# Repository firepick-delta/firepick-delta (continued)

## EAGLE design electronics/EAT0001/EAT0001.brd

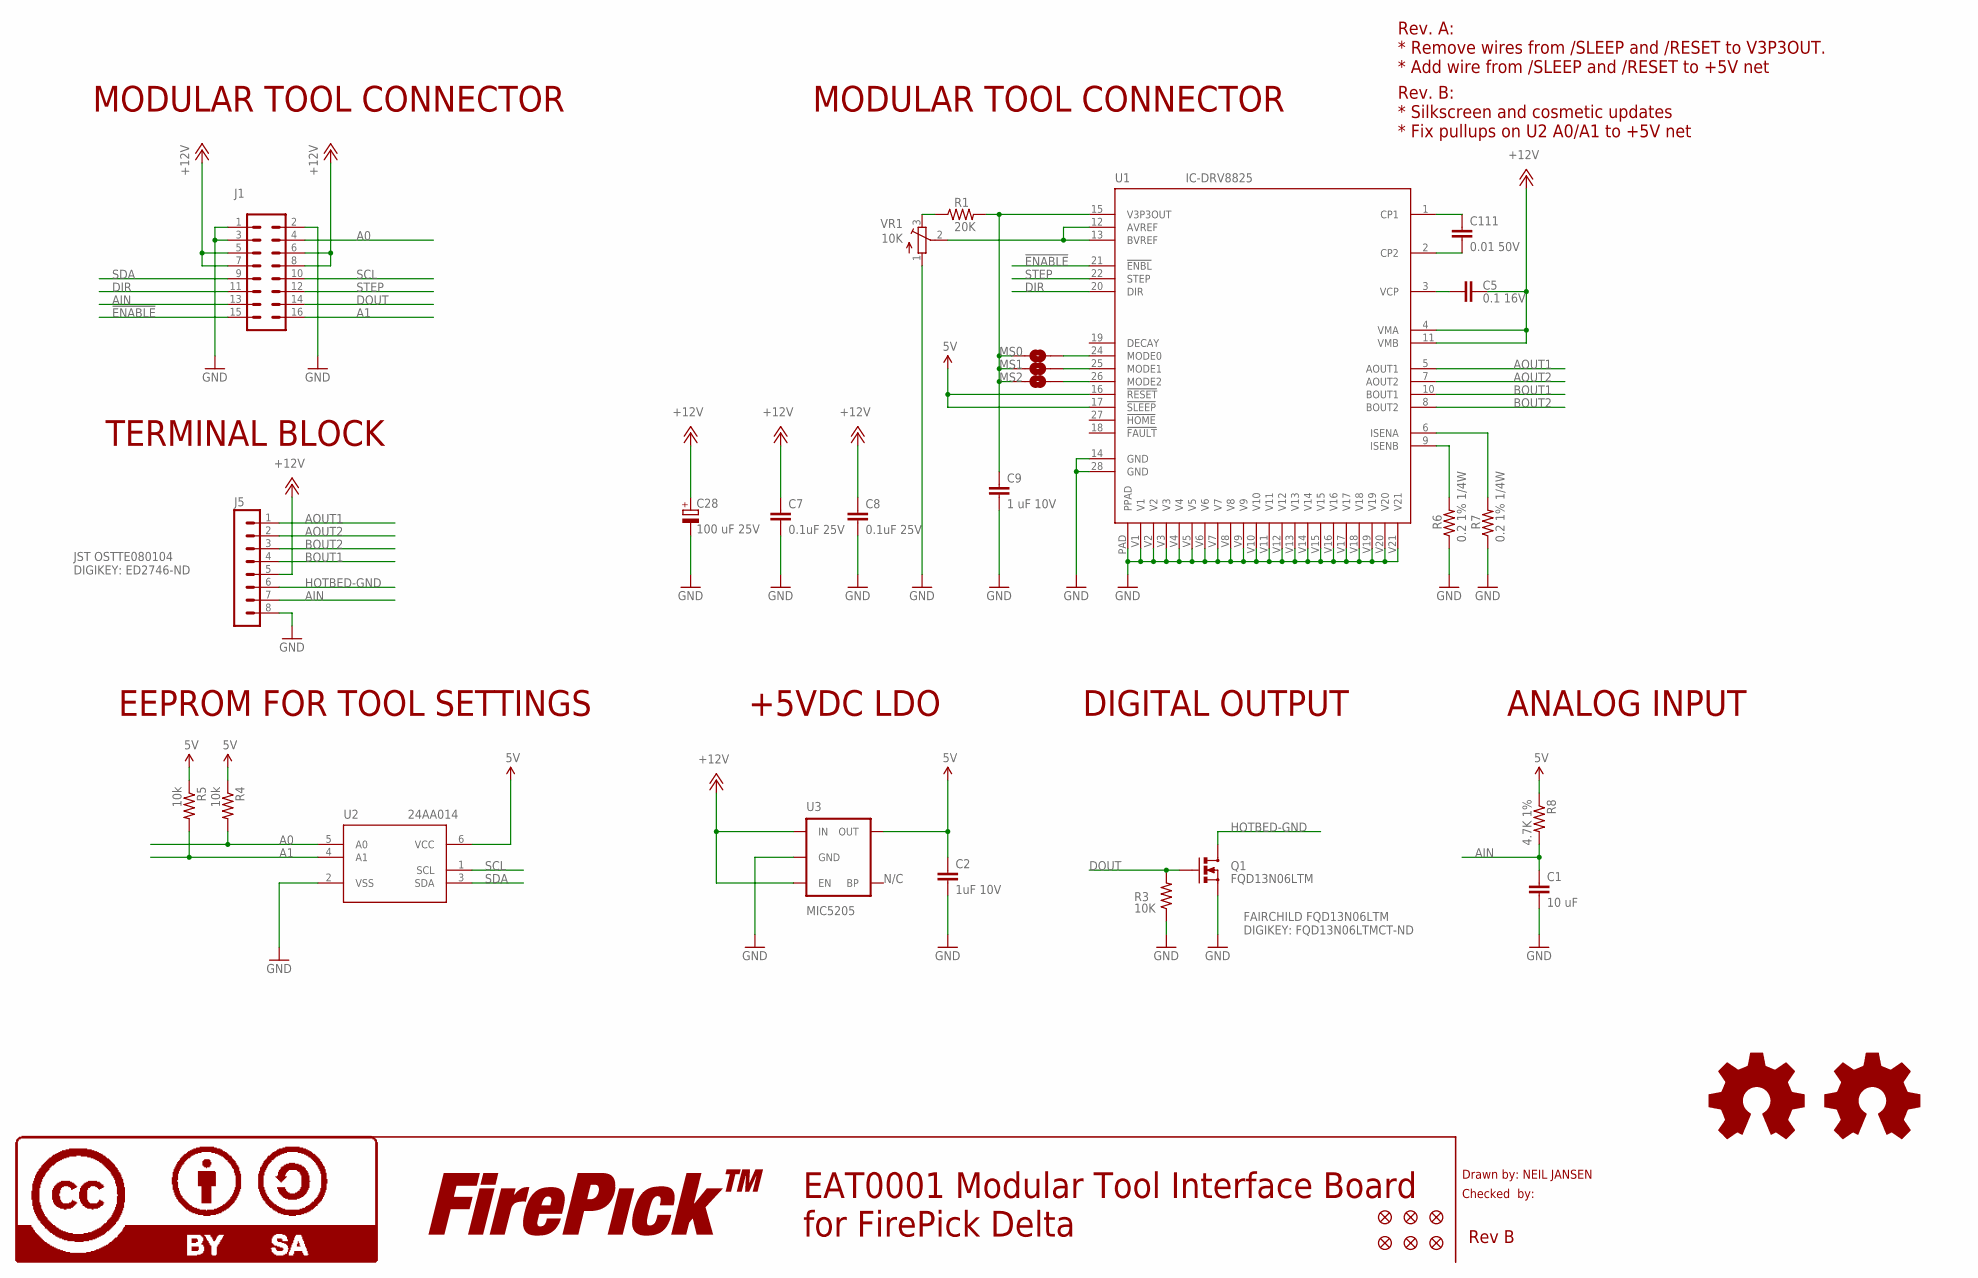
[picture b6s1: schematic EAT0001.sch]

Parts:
C1: 10 uF; 0805
C2: 1uF 10V; 0805
C5: 0.1 16V; 0805
C7, C8: 0.1uF 25V; 0805
C9: 1 uF 10V; 0805
C28: 100 uF 25V; UD-6,3X7,7_NICHICON
C111: 0.01 50V; 0805
FID1, FID2, FID3, FID4, FID5, FID6: FIDUCIAL1X2; FIDUCIAL-1X2
J1: CONN-RECT-16PIN-2ROWSIDE; CONN-RECT-2.54MM-16PIN-2ROW-SIDE
J5: CONN-OSTTE1201X4
LOGO1, LOGO5: LOGO-OSHWSMALL; LOGO-OSHW-SMALL
LOGO4: LOGO-FIREPICKMEDIUM; LOGO-FIREPICK-MEDIUM
LOGO6: LOGO-CC-BY-SAMEDIUM; LOGO-CC-BY-SA-MEDIUM
MS0, MS1, MS2: JUMPER; JUMPER-NC
Q1: FQD13N06LTM; DPAK
R1: 20K; 0805
R3: 10K; 0805
R4, R5: 10k; 0805
R6, R7: 0.2 1% 1/4W; 0805
R8: 4.7K 1%; 0805
U1: IC-DRV8825; TSSOP28_PAD
U2: 24AA014; SOT23-6
U3: MIC5205; SOT23-5
VR1: 10K; TC33X

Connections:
5V: C2.1, R4.1, R5.1, R8.1, U1.16 (!RESET), U1.17 (!SLEEP), U2.6 (VCC), U3.5 (OUT)
!ENABLE: J1.15, U1.21 (!ENBL)
+12V: C5.1, C7.1, C8.1, C28.+, J1.5, J1.6, J1.7, J1.8, J5.5, U1.4 (VMA), U1.11 (VMB), U3.1 (IN), U3.3 (EN)
A0: J1.4, R4.2, U2.5 (A0)
A1: J1.16, R5.2, U2.4 (A1)
AIN: C1.1, J1.13, J5.7, R8.2
AOUT1: J5.1, U1.5 (AOUT1)
AOUT2: J5.2, U1.7 (AOUT2)
BOUT1: J5.4, U1.10 (BOUT1)
BOUT2: J5.3, U1.8 (BOUT2)
CP1: C111.1, U1.1 (CP1)
CP2: C111.2, U1.2 (CP2)
DIR: J1.11, U1.20 (DIR)
DOUT: J1.14, Q1.1 (G), R3.2
GND: C1.2, C2.2, C7.2, C8.2, C9.2, C28.-, J1.1, J1.2, J1.3, J5.8, Q1.3 (S), R3.1, R6.1, R7.1, U1.14 (GND), U1.28 (GND), U1.PAD, U1.V1, U1.V2, U1.V3, U1.V4, U1.V5, U1.V6, U1.V7, U1.V8, U1.V9, U1.V10, U1.V11, U1.V12, U1.V13, U1.V14, U1.V15, U1.V16, U1.V17, U1.V18, U1.V19, U1.V20, U1.V21, U2.2 (VSS), U3.2 (GND), VR1.1 (A)
HOTBED-GND: J5.6, Q1.4 (D)
ISENA: R7.2, U1.6 (ISENA)
ISENB: R6.2, U1.9 (ISENB)
MOD1: MS1.2, U1.25 (MODE1)
MODE0: MS0.2, U1.24 (MODE0)
MODE2: MS2.2, U1.26 (MODE2)
unnamed: R1.1, VR1.3 (E)
SCL: J1.10, U2.1 (SCL)
SDA: J1.9, U2.3 (SDA)
STEP: J1.12, U1.22 (STEP)
V3P3OUT: C9.1, MS0.1, MS1.1, MS2.1, R1.2, U1.15 (V3P3OUT)
VCP: C5.2, U1.3 (VCP)
VREF: U1.12 (AVREF), U1.13 (BVREF), VR1.2 (S)

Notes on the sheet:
Drawn by: NEIL JANSEN
Checked by:
Rev B
EAT0001 Modular Tool Interface Board for FirePick Delta
MODULAR TOOL CONNECTOR
DIGITAL OUTPUT
EEPROM FOR TOOL SETTINGS
ANALOG INPUT
N/C
+5VDC LDO
JST OSTTE080104 DIGIKEY: ED2746-ND
TERMINAL BLOCK
FAIRCHILD FQD13N06LTM DIGIKEY: FQD13N06LTMCT-ND
Rev. A: * Remove wires from /SLEEP and /RESET to V3P3OUT. * Add wire from /SLEEP and /RESET to +5V net
Rev. B: * Silkscreen and cosmetic updates * Fix pullups on U2 A0/A1 to +5V net

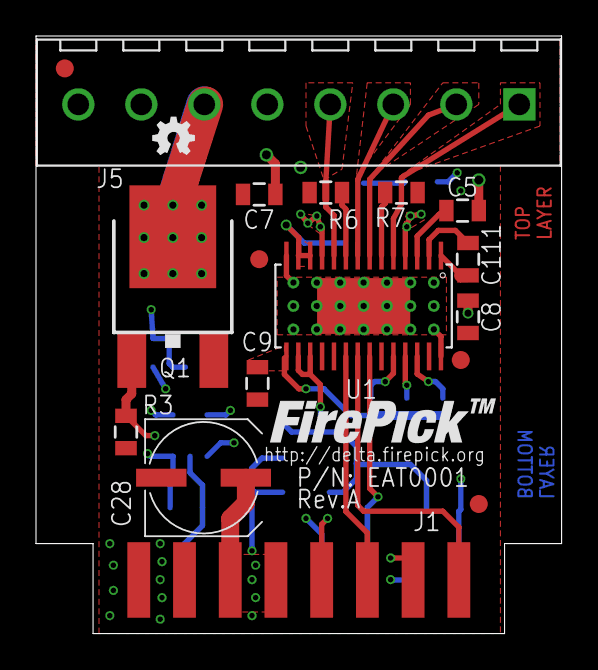
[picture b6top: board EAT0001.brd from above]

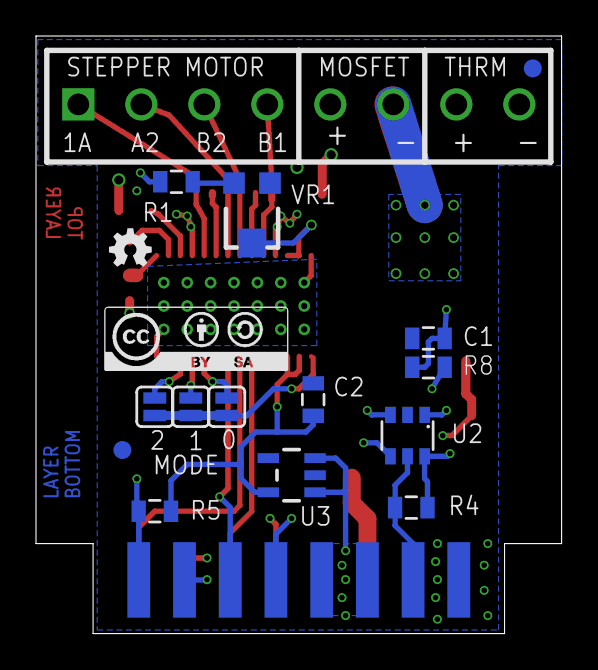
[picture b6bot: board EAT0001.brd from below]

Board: 4 copper layers, 29.2 x 33.2 mm, 35 parts (16 on the bottom side), 28 nets.

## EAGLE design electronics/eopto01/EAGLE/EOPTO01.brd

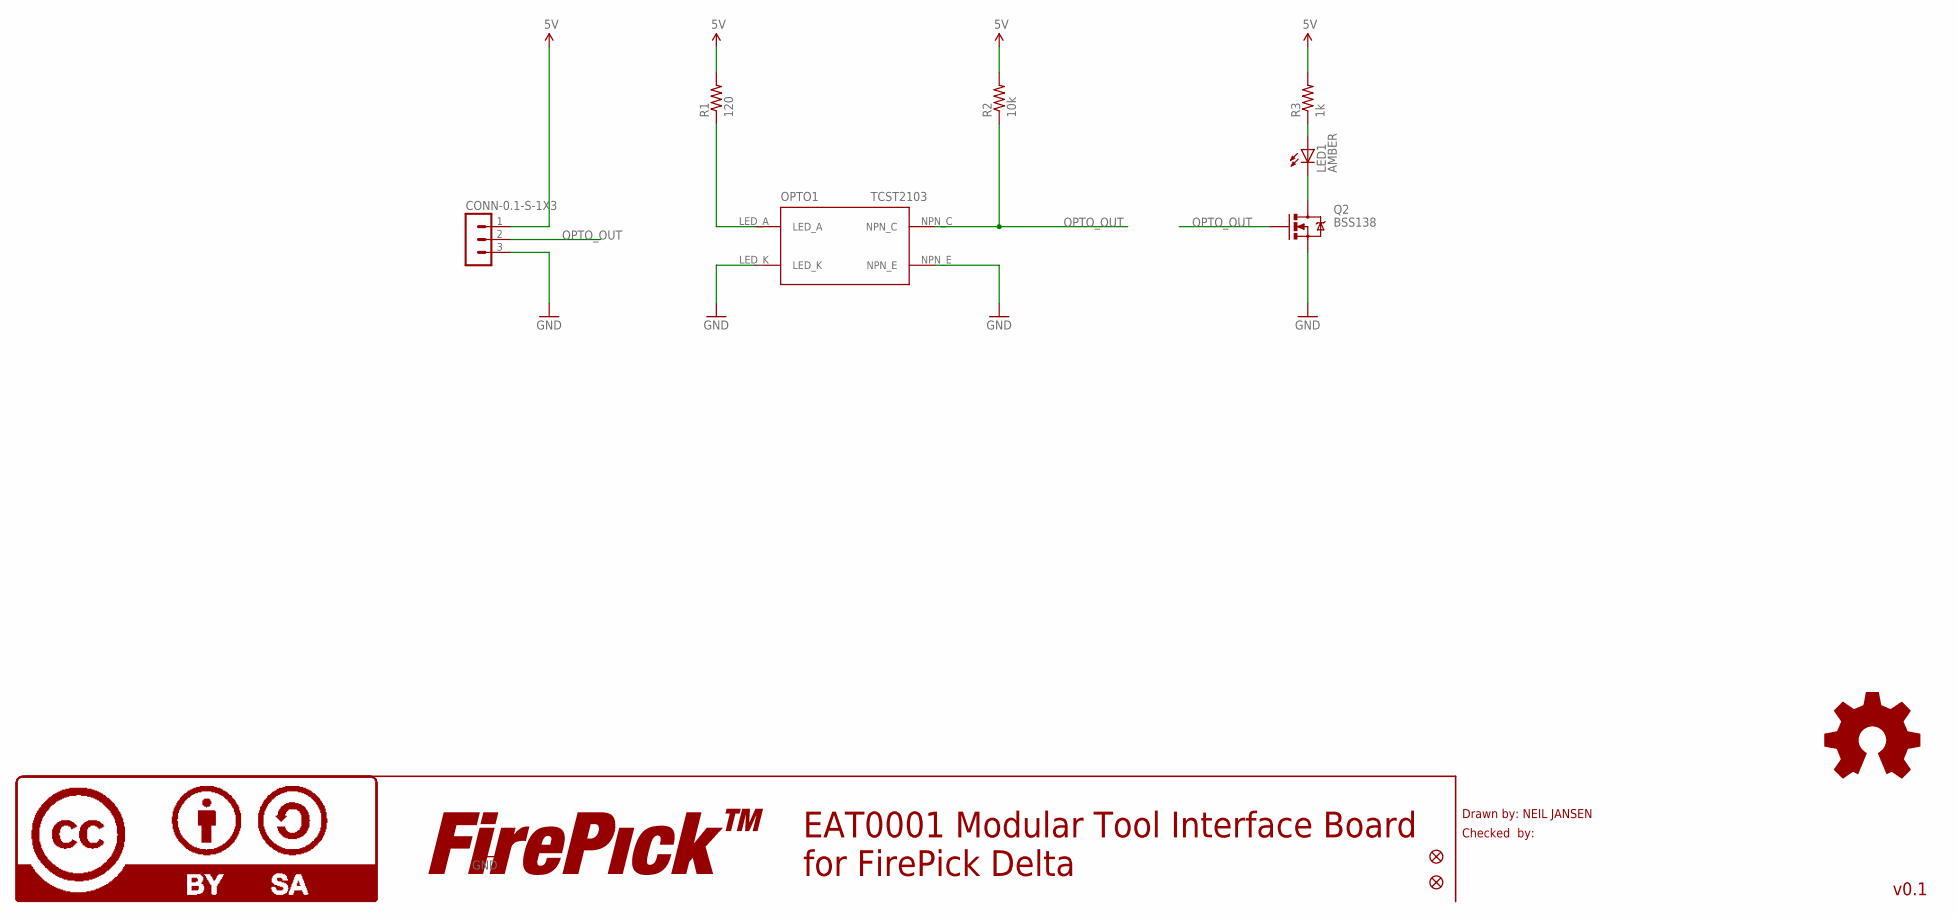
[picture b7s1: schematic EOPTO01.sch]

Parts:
FID3, FID4: FIDUCIAL1X2; FIDUCIAL-1X2
J1: CONN-0.1-S-1X3; MA03-1; PARTNO CONN-0.1-RA-1X3
LED1: AMBER; LED-1206; PARTNO LTST-C150AKT
LOGO4: LOGO-FIREPICKMEDIUM; LOGO-FIREPICK-MEDIUM
LOGO5: LOGO-OSHWSMALL; LOGO-OSHW-SMALL
LOGO6: LOGO-CC-BY-SAMEDIUM; LOGO-CC-BY-SA-MEDIUM
OPTO1: TCST2103; TCST2013; PARTNO TCST2103
Q2: BSS138; SOT23; PARTNO BSS138
R1: 120; 0805; PARTNO RC0805FR-07120RL
R2: 10k; 0805; PARTNO RC0805FR-0710KL
R3: 1k; 0805; PARTNO RC0805FR-071KL

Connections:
5V: J1.1, R1.2, R2.2, R3.2
GND: J1.3, OPTO1.LED_K, OPTO1.NPN_E, Q2.2 (S)
unnamed: LED1.C, Q2.3 (D)
unnamed: LED1.A, R3.1
unnamed: OPTO1.LED_A, R1.1
OPTO_OUT: J1.2, OPTO1.NPN_C, Q2.1 (G), R2.1

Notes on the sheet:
Drawn by: NEIL JANSEN
Checked by:
v0.1
EAT0001 Modular Tool Interface Board for FirePick Delta

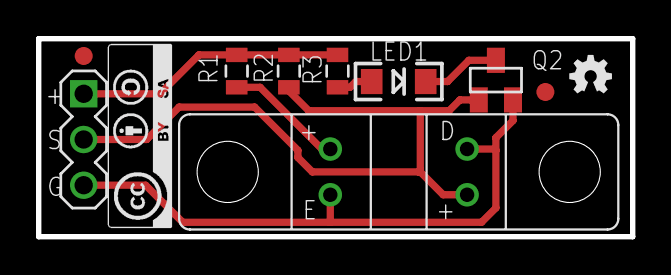
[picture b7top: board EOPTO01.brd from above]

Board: 2 copper layers, 33.0 x 11.0 mm, 12 parts (1 on the bottom side), 6 nets.

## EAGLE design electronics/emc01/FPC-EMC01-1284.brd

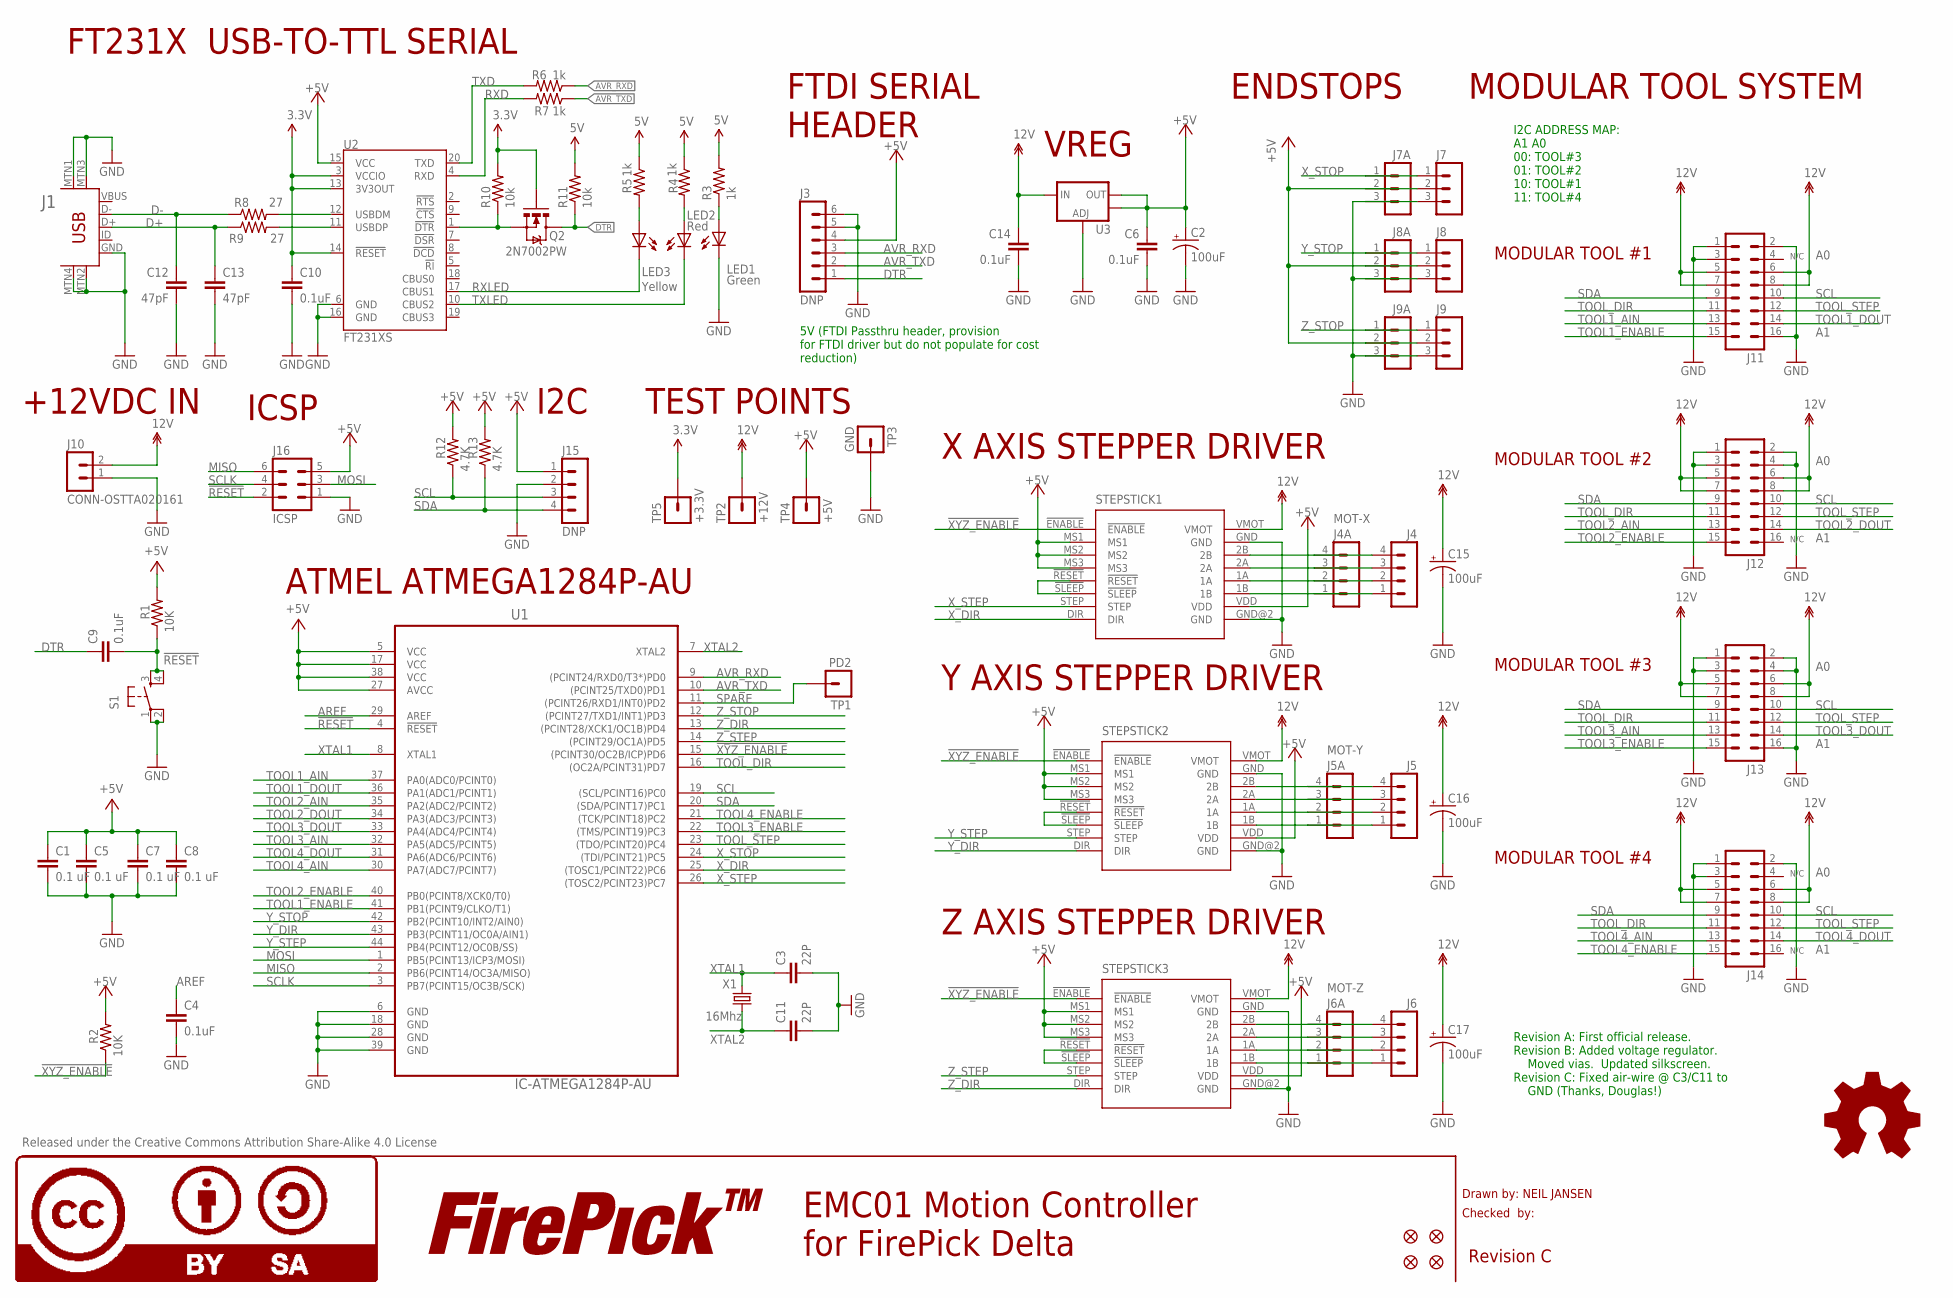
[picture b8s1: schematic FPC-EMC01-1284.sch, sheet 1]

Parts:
C1, C5, C7, C8: 0.1 uF; 0805
C2, C15, C16, C17: 100uF; PANASONIC_D
C3, C11: 22P; 0805
C4, C6, C9, C10, C14: 0.1uF; 0805
C12, C13: 47pF; 0805
FID1, FID2, FID3, FID4: FIDUCIAL1X2; FIDUCIAL-1X2
J1: USB-MINIB-5PIN; USB-MINIB
J3: DNP; MA06-1
J4, J5, J6: MA04-1
J4A: MOT-X; CONN-JST-PH_2.0MM_4PIN-SMT-RA
J5A: MOT-Y; CONN-JST-PH_2.0MM_4PIN-SMT-RA
J6A: MOT-Z; CONN-JST-PH_2.0MM_4PIN-SMT-RA
J7, J8, J9: MA03-1
J7A, J8A, J9A: CONN-RECT-3PINJST_PH_2MM; CONN-JST_PH-2.0MM-3PIN-SMT-RA
J10: CONN-OSTTA020161
J11, J12, J13, J14: CONN-RECT-16PIN-2ROW; CONN-RECT-2.54MM-16PIN-2ROW-SMTH
J15: DNP; MA04-1
J16: ICSP; CONN-RECT-2.54MM-6-PIN-2ROW-SMTH
LED1: Green; LED-1206-NO_SILK
LED2: Red; LED-1206-NO_SILK
LED3: Yellow; LED-1206-NO_SILK
LOGO4: LOGO-FIREPICK
LOGO5: LOGO-OSHWMEDIUM; LOGO-OSHW-MEDIUM
LOGO6: LOGO-CC-BY-SA
Q2: 2N7002PW; SOT323
R1, R2: 10K; 0805
R3, R4, R5, R6, R7: 1k; 0805
R8, R9: 27; 0805
R10, R11: 10k; 0805
R12, R13: 4.7K; 0805
S1: TAC_SWITCHSMD; TACTILE_SWITCH_SMD
STEPSTICK1, STEPSTICK2, STEPSTICK3: STEPSTICK
TP1: PD2; CON-TESTPOINT
TP2: +12V; CON-TESTPOINT
TP3: GND; CON-TESTPOINT
TP4: +5V; CON-TESTPOINT
TP5: +3.3V; CON-TESTPOINT
U1: IC-ATMEGA1284P-AU; QFP44
U2: FT231XS; SSOP20_L
U3: V_REG_LM1117SOT223; SOT223
X1: 16Mhz; CTS406

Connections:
3.3V: C10.1, Q2.1 (G), R10.2, TP5.1, U2.3 (VCCIO), U2.13 (3V3OUT), U2.14 (!RESET)
12V: C14.1, C15.+, C16.+, C17.+, J10.2, J11.5, J11.6, J11.7, J11.8, J12.5, J12.6, J12.7, J12.8, J13.5, J13.6, J13.7, J13.8, J14.5, J14.6, J14.7, J14.8, STEPSTICK1.VMOT, STEPSTICK2.VMOT, STEPSTICK3.VMOT, TP2.1, U3.3 (IN)
!RESET: C9.2, J16.2, R1.1, S1.3, S1.4, U1.4 (!RESET)
!XYZ_ENABLE: R2.1, STEPSTICK1.!ENABLE!, STEPSTICK2.!ENABLE!, STEPSTICK3.!ENABLE!, U1.15 ((PCINT30/OC2B/ICP)PD6)
+5V: C1.1, C2.+, C5.1, C6.1, C7.1, C8.1, J3.4, J7.2, J7A.2, J8.2, J8A.2, J9.2, J9A.2, J15.1, J16.5, R1.2, R2.2, R3.2, R4.1, R5.1, R11.2, R12.2, R13.2, STEPSTICK1.MS1, STEPSTICK1.MS2, STEPSTICK1.MS3, STEPSTICK1.VDD, STEPSTICK2.MS1, STEPSTICK2.MS2, STEPSTICK2.MS3, STEPSTICK2.VDD, STEPSTICK3.MS1, STEPSTICK3.MS2, STEPSTICK3.MS3, STEPSTICK3.VDD, TP4.1, U1.5 (VCC), U1.17 (VCC), U1.27 (AVCC), U1.38 (VCC), U2.15 (VCC), U3.2 (OUT), U3.4 (OUT)
AREF: C4.1, U1.29 (AREF)
AVR_RXD: J3.3, R6.1, U1.9 ((PCINT24/RXD0/T3*)PD0)
AVR_TXD: J3.2, R7.1, U1.10 ((PCINT25/TXD0)PD1)
D+: C13.1, J1.D+, R9.1
D-: C12.1, J1.D-, R8.1
DTR: C9.1, J3.1, Q2.3 (D), R11.1
DTR_3.3V: Q2.2 (S), R10.1, U2.1 (!DTR)
GND: C1.2, C2.-, C3.2, C4.2, C5.2, C6.2, C7.2, C8.2, C10.2, C11.2, C12.2, C13.2, C14.2, C15.-, C16.-, C17.-, J1.GND, J1.MTN1 (MTN2), J1.MTN2 (MTN3), J1.MTN3 (MTN1), J1.MTN4, J3.5, J3.6, J7.3, J7A.3, J8.3, J8A.3, J9.3, J9A.3, J10.1, J11.1, J11.2, J11.3, J11.16, J12.1, J12.2, J12.3, J12.4, J13.1, J13.2, J13.3, J13.4, J13.16, J14.1, J14.2, J14.3, J15.2, J16.1, LED1.C, S1.1, S1.2, STEPSTICK1.GND, STEPSTICK1.GND@2 (GND), STEPSTICK2.GND, STEPSTICK2.GND@2 (GND), STEPSTICK3.GND, STEPSTICK3.GND@2 (GND), TP3.1, U1.6 (GND), U1.18 (GND), U1.28 (GND), U1.39 (GND), U2.6 (GND), U2.16 (GND), U3.1 (ADJ)
MISO: J16.6, U1.2 (PB6(PCINT14/OC3A/MISO))
MOSI: J16.3, U1.1 (PB5(PCINT13/ICP3/MOSI))
unnamed: LED1.A, R3.1
unnamed: STEPSTICK1.!RESET!, STEPSTICK1.!SLEEP!
unnamed: STEPSTICK2.!RESET!, STEPSTICK2.!SLEEP!
unnamed: LED2.A, R4.2
unnamed: LED3.A, R5.2
unnamed: R8.2, U2.12 (USBDM)
unnamed: STEPSTICK3.!RESET!, STEPSTICK3.!SLEEP!
unnamed: R9.2, U2.11 (USBDP)
RXD: R7.2, U2.4 (RXD)
RXLED: LED3.C, U2.17 (CBUS1)
SCL: J11.10, J12.10, J13.10, J14.10, J15.3, R12.1, U1.19 ((SCL/PCINT16)PC0)
SCLK: J16.4, U1.3 (PB7(PCINT15/OC3B/SCK))
SDA: J11.9, J12.9, J13.9, J14.9, J15.4, R13.1, U1.20 ((SDA/PCINT17)PC1)
SPARE: TP1.1, U1.11 ((PCINT26/RXD1/INT0)PD2)
TOOL1_AIN: J11.13, U1.37 (PA0(ADC0/PCINT0))
TOOL1_DOUT: J11.14, U1.36 (PA1(ADC1/PCINT1))
TOOL1_ENABLE: J11.15, U1.41 (PB1(PCINT9/CLKO/T1))
TOOL2_AIN: J12.13, U1.35 (PA2(ADC2/PCINT2))
TOOL2_DOUT: J12.14, U1.34 (PA3(ADC3/PCINT3))
TOOL2_ENABLE: J12.15, U1.40 (PB0(PCINT8/XCK0/T0))
TOOL3_AIN: J13.13, U1.32 (PA5(ADC5/PCINT5))
TOOL3_DOUT: J13.14, U1.33 (PA4(ADC4/PCINT4))
TOOL3_ENABLE: J13.15, U1.22 ((TMS/PCINT19)PC3)
TOOL4_AIN: J14.13, U1.30 (PA7(ADC7/PCINT7))
TOOL4_DOUT: J14.14, U1.31 (PA6(ADC6/PCINT6))
TOOL4_ENABLE: J14.15, U1.21 ((TCK/PCINT18)PC2)
TOOL_DIR: J11.11, J12.11, J13.11, J14.11, U1.16 ((OC2A/PCINT31)PD7)
TOOL_STEP: J11.12, J12.12, J13.12, J14.12, U1.23 ((TDO/PCINT20)PC4)
TXD: R6.2, U2.20 (TXD)
TXLED: LED2.C, U2.10 (CBUS2)
X1A: J4.2, J4A.2, STEPSTICK1.1A
X1B: J4.1, J4A.1, STEPSTICK1.1B
X2A: J4.3, J4A.3, STEPSTICK1.2A
X2B: J4.4, J4A.4, STEPSTICK1.2B
XTAL1: C3.1, U1.8 (XTAL1), X1.3 (2)
XTAL2: C11.1, U1.7 (XTAL2), X1.1
X_DIR: STEPSTICK1.DIR, U1.25 ((TOSC1/PCINT22)PC6)
X_STEP: STEPSTICK1.STEP, U1.26 ((TOSC2/PCINT23)PC7)
X_STOP: J7.1, J7A.1, U1.24 ((TDI/PCINT21)PC5)
Y1A: J5.2, J5A.2, STEPSTICK2.1A
Y1B: J5.1, J5A.1, STEPSTICK2.1B
Y2A: J5.3, J5A.3, STEPSTICK2.2A
Y2B: J5.4, J5A.4, STEPSTICK2.2B
Y_DIR: STEPSTICK2.DIR, U1.43 (PB3(PCINT11/OC0A/AIN1))
Y_STEP: STEPSTICK2.STEP, U1.44 (PB4(PCINT12/OC0B/SS))
Y_STOP: J8.1, J8A.1, U1.42 (PB2(PCINT10/INT2/AIN0))
Z1A: J6.2, J6A.2, STEPSTICK3.1A
Z1B: J6.1, J6A.1, STEPSTICK3.1B
Z2A: J6.3, J6A.3, STEPSTICK3.2A
Z2B: J6.4, J6A.4, STEPSTICK3.2B
Z_DIR: STEPSTICK3.DIR, U1.13 ((PCINT28/XCK1/OC1B)PD4)
Z_STEP: STEPSTICK3.STEP, U1.14 ((PCINT29/OC1A)PD5)
Z_STOP: J9.1, J9A.1, U1.12 ((PCINT27/TXD1/INT1)PD3)

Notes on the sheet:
I2C ADDRESS MAP: A1 A0 00: TOOL#3 01: TOOL#2 10: TOOL#1 11: TOOL#4
MODULAR TOOL #4
MODULAR TOOL #3
MODULAR TOOL #2
MODULAR TOOL #1
5V (FTDI Passthru header, provision for FTDI driver but do not populate for cost reduction)
Drawn by: NEIL JANSEN
Checked by:
Revision C
EMC01 Motion Controller for FirePick Delta
ATMEL ATMEGA1284P-AU
FT231X USB-TO-TTL SERIAL
X AXIS STEPPER DRIVER
ENDSTOPS
MODULAR TOOL SYSTEM
FTDI SERIAL HEADER
+12VDC IN
ICSP
I2C
TEST POINTS
N/C
Y AXIS STEPPER DRIVER
Z AXIS STEPPER DRIVER
Released under the Creative Commons Attribution Share-Alike 4.0 License
VREG
Revision A: First official release. Revision B: Added voltage regulator. Moved vias. Updated silkscreen. Revision C: Fixed air-wire @ C3/C11 to GND (Thanks, Douglas!)

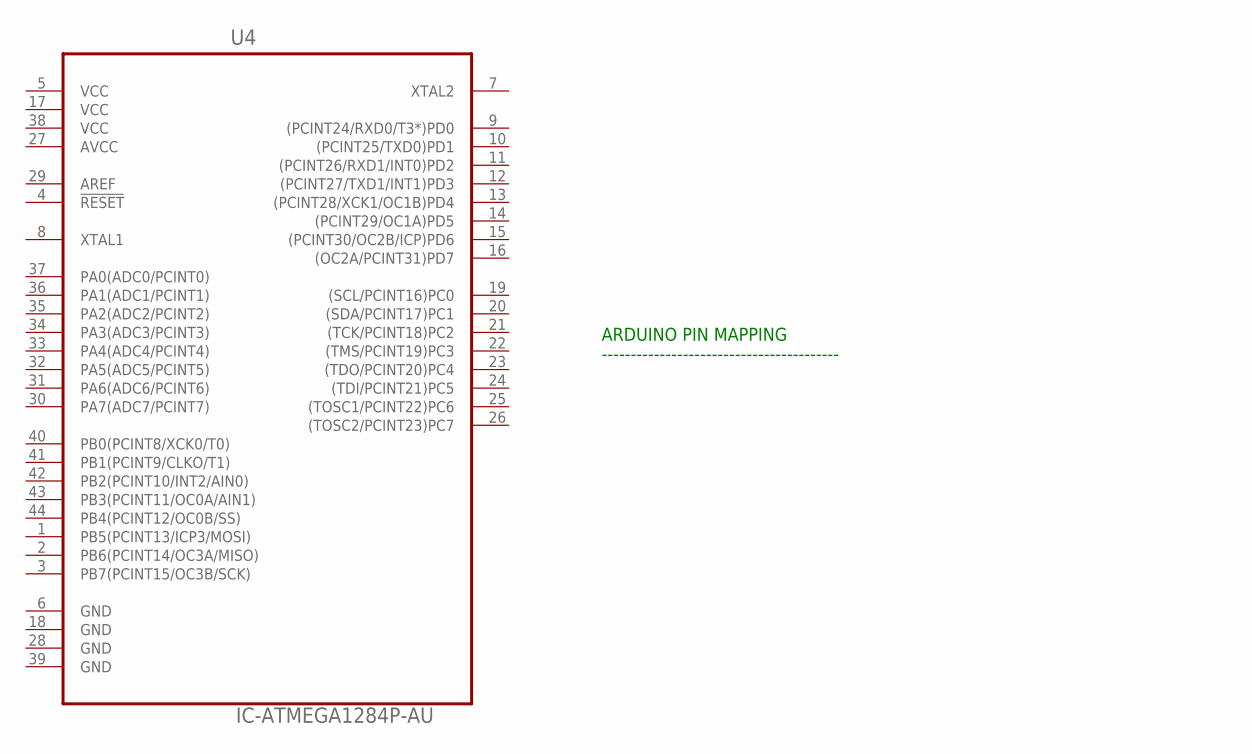
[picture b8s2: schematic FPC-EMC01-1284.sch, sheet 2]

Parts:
U4: IC-ATMEGA1284P-AU; QFP44

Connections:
AVCC: U4.27 (AVCC)
VCC: U4.5 (VCC), U4.17 (VCC), U4.38 (VCC)

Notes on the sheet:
ARDUINO PIN MAPPING -----------------------------------------

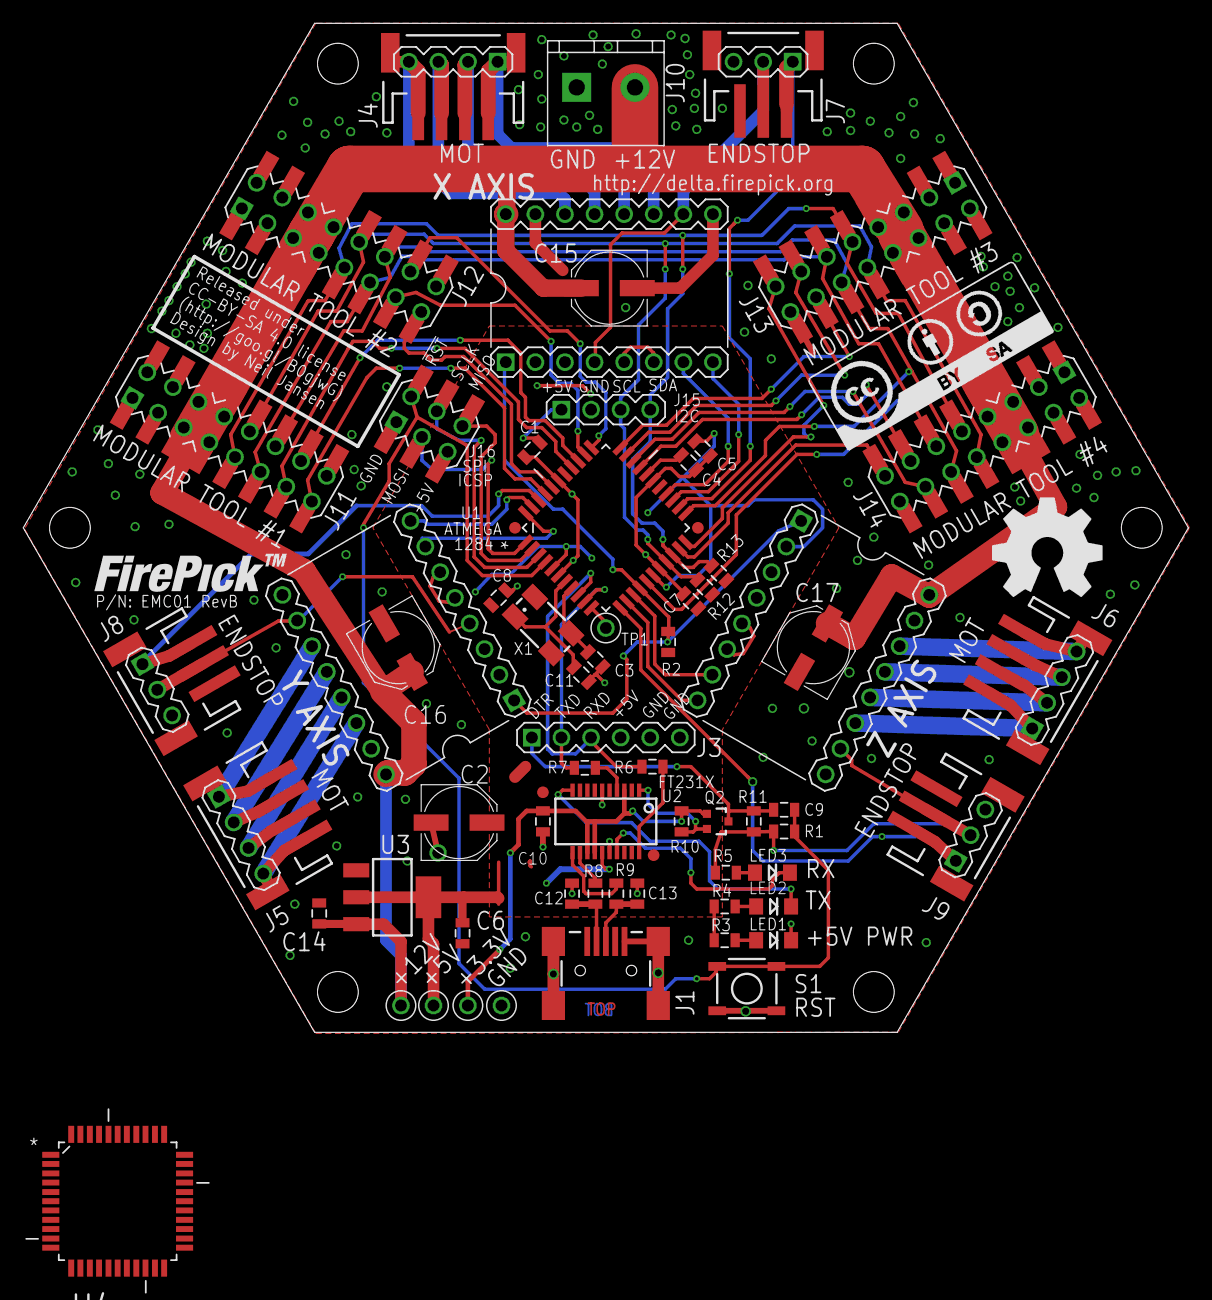
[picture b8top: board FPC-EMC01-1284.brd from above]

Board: 2 copper layers, 100.0 x 86.6 mm, 76 parts (0 on the bottom side), 69 nets.

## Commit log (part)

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2014-06-12 initial
2014-06-13 adding new PCB
2014-06-13 updating PCB
2014-06-13 updating PCB and adding GERBERS+BOM
2014-06-13 Fixed silkscreen and updated gerbers to final rev
2014-06-16 Rev. A for RS485 to Servo and Accelerometer
2014-06-17 Rev. A PCB HDMI to FPC converter, for RPi Cam
2014-06-17 Removed unused components from schematic, added WS2812 LED, changed C18 to C17
2014-06-17 Added components reference to silkscreen
2014-06-17 Added title to worksheet for SCH, added image of PCB and PDF of schematic
2014-06-17 Added schematic PDF and image of PCB
2014-06-17 Added reference for C11 & C12
2014-06-18 Added resistor for WS2812 onboard LED, connected to the right input
2014-06-18 Differential traces are length matched now
2014-06-23 New chip and layout + A axis motor controller/Board still not finalized
2014-06-23 adding new PDF
2014-06-23 adding new unfinished PCB
2014-06-24 adding some used libraries
2014-06-24 updated pinouts
2014-06-24 Added modular tool connectors, RasPi connector, Front Panel connector. 
2014-06-24 Fixed File
2014-06-24 no edit
2014-06-24 recover lost changes
2014-06-24 Revert "recover lost changes"
    This reverts commit 0ce016bf4596014ad1f4ff05d6638003136b1386.
2014-06-24 Restore Neil's changes 1d1a
2014-06-24 adding Dayton's 5958 ICSP/Power circuits to Neil's board
2014-06-24 rename with dashes
2014-06-24 Fixed schematics
    looks more uniform
2014-06-24 New Library
2014-06-24 Added FFC connector from HDMI
2014-06-24 Fixed errors/connectors
    Fixed the ERC errors, ones that are left just ignore. Neil needs to add
    his library of proper JST connectors to the board and we will be pretty
    much ready to route.
2014-06-24 added updated PDF
2014-06-25 Adding new FirePick-approved library
2014-06-25 Added connectors for prototype FirePick Delta motion controller board Rev.1
2014-06-26 Added pcb outline for FPC-EMC01-1284.brd, and placed connectors per AutoCAD DXF. Added male 16-pin connector to firepick.lbr.
2014-06-26 Moved stepper driver IC's to symmetrically-pleasing locations
2014-06-26 minor tweaks before layout
2014-06-26 Routed J15-J1
2014-07-02 Update README.md
    added links to other important repos
2014-07-04 Changed connector on LCD board. Added notes to EMC01 board.
2014-07-06 Wired up encoder, switches, and LEDs
2014-07-07 Redesigned with Micro USB instead of Microfit. PCB is now smaller. Using I2C to communicate with motion controller
2014-07-09 modifying gitignore to ignore temp vim files
2014-07-11 adding bom markdown generation scripts, testing FireBOM URL /github path
2014-07-11 moving BOM to firepick-delta.wiki
2014-07-11 KiCAD version of the opto-endstop. Adding transistor for LED
2014-07-11 Forgot how to Eagle, but added DC/DC. Change components for better specs
2014-07-12 Added JST connector for Opto-endstop
2014-07-14 Added StepStick to library, and updated EMC01 schematic/pcb
2014-07-15 fixing I2C connectors, adding FTDI, adding sch for motor controllers
2014-07-15 Changed to Sparkfun Micro USB connector
2014-07-17 board partially routed
2014-07-17 emc01 routing update
2014-07-18 polygonception
2014-07-18 routing update
2014-07-26 deleting directory '3d'
2014-07-28 some extra routing
2014-07-30 Adding mechanical parts
2014-07-30 adding dummy files so to create empty directories
2014-07-30 adding creative commons CC-BY-SA license to mechanical files
2014-07-31 - Added FPD main assembly AFPD0001 - FirePick Delta Hacker-Developer Edition.AD_ASM - Connected carbon rod delta linkages
2014-07-31 Adding STL's for 3d printed files
2014-07-31 added jigs/fixtures, adding component feeder mount assembly
2014-08-01 Adding 2D prints and DXF's for acrylic frame plates
2014-08-01 New end effector stuff
2014-08-01 updating top-level README.md to include creative-commons png and other useful info
2014-08-01 adding fasteners to frame, still playing with end effector cam/hdmi board
2014-08-01 Finished adding T-nuts to frame
2014-08-01 Fixing issue where Cubify was bitching about problems encountered while loading AD0001 - Frame.AD_ASM
2014-08-02 Adding feeder mounts to AFPD0001 - FirePick Delta Hacker-Developer Edition.AD_ASM
2014-08-02 Adding pretty things to EMC01.AD_ASM
2014-08-02 Adding stuff for SMT nozzle, and checking in some stuff that I somehow missed
2014-08-02 Moved EMC01 to assembly
2014-08-02 Importing Raspberry Pi STL model downloaded from: http://www.inti-innovations.co.uk/products/inti-media/inti-media-raspberrypi.html
2014-08-03 Created RasPi HAT for camera pass-through and LCD/buttons. Prettied up RasPi Model B+ model.
2014-08-12 Changed power connector from 3-pin to 2-pin
2014-08-13 - Swapped FT232RL for FT231XS (copied/pasted to Sparkfun RedBoard) - Replaced micro USB with mini USB - Deleted second micro USB and Z probe pin (we can use a modular connector Z probe instead rather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
2014-08-14 Adding lots of new SMT component feeders and stuff!
2014-08-14 Fixed 608 bearing block nut trap clearance Fixed bottom plate, added clearance slots for Misumi diagonal braces, which have alignment tabs.
2014-08-14 Updated 608 bearing block STL and bottom plate DXF after making fixes from last commit
2014-08-18 FPD parts
    Brackets and Plates
2014-08-18 corner bracket
2014-08-18 3D0051.stl
2014-08-18 Transcribed Eagle schematic to KiCAD with some minor, mostly asthetic changes and added RPi GPIOs for the encoder, buttons and LEDs. Imported Christian's HDMItoFFC adapter for the PiCam.
2014-08-18 Imported the Eagle board file to KiCAD. Found a place for everthing. Switched places between the power JST and the encoder JST. Routed everything. Matched trace lengths for HDMI to FFC PiCam adapter.
2014-08-18 3D0051
2014-08-18 3D0051.stl.zip
2014-08-18 STL as binary
2014-08-21 3D0456-final-draft
2014-08-25 saving intermediate
2014-08-25 constraints
2014-08-26 autorouting v1
2014-08-26 autorouting v2 w/ groundplane
2014-08-27 constraints (really)
2014-08-27 plated updated cubify model
2014-08-28 Changed to correct pinout for Type A HDMI
2014-08-28 PushPlastics orange 3mm PLA @ 220C/60-50C TAZ4. 2.5hrs
2014-08-30 Loose Fit for delta drive parts
2014-09-02 Cleaned up EMC01 board and finalized for peer review
2014-09-03 Cleaned up ERPIHAT01 board and finalized for peer review
2014-09-03 Cleanups after peer review
2014-09-03 Forgot some labels
2014-09-04 Print tested TAZ.
2014-09-04 Fixed minor issues and changed modular tool connector pinout to allow better routing of GND and +12V planes
2014-09-07 Updated EAGLE library for firepick-specific stuff
2014-09-07 Updated all EAGLE PCB's for first Prototype production run.
2014-09-07 cleanup
2014-09-09 REVISION A of EMC01 board. Fixed unconnected wires on TOOL1_ENABLE, TOOL2_ENABLE, TOOL3_ENABLE, and TOOL4_ENABLE. This was discovered by Seeed Studio Fusion PCB service after being submitted to be ma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
2014-09-10 RasPiCam wrench; 3mm effector rod holes
2014-09-10 Moved wrench to Jigs and renamed to fit Neil's numbering
2014-09-10 Forgot STL
2014-09-10 LC Hook
2014-09-10 Renamed to remove extra zero
2014-09-10 More zeros
2014-09-11 Legacy HW mounts (Mega, RPi B)
2014-09-12 Mirror plate. A calibration hunch. Let's see where it goes...
2014-09-12 Mirror plate calibration hunch
2014-09-24 Minor tweaks
2014-09-24 Cleaned up in NetFabb
2014-09-24 Merged in STL fix for 3D0051 from dev-loose
2014-09-26 Changed to MOSFET for LED
2014-10-01 adding new PCB rev
2014-10-02 Revision A, after assembling first batch of PCBs.
2014-10-05 Added link to FireBOM AFPD0001 page
2014-10-06 adding list of contributors and maintainers
2014-10-08 * New Ball-stud delta rods * Updates for new PCB assemblies * Updates for LCD bezel assembly * Updates for modular tools * Other misc stuff
2014-10-08 Adding LCD bezel, fixing corner brackets
2014-10-10 Updated delta mechanism, feeders. Added magnetic bed.
2014-10-10 Updating all STLs
2014-10-10 updating markdown with new contributers :)
2014-10-10 Sproing
2014-10-12 more cool stuff
2014-10-12 Updating feeder design... seems somewhat usable now :-/
2014-10-22 Continuing work on feeders, cameras, and other misc mechanical pieces
2014-10-23 Full Rod
2014-10-23 Added a chopped up version of the top plate that you can print on a Taz sized 3d printer.
2014-10-24 Improved blender file to make it more procedural. The meshes intended for export are now laregely made with modifiers.
2014-10-24 Moved hole on corner. Removed fluff. Its now threads into the center of the vertical extrusion just like the rubber feet. Generated with the improved blender file, and ended up removing unnecessary f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
2014-10-24 Enlarged holes to 5.5 mm to fit M5 bolts. Oops All holes to attatch to the frame are additionally positioned using modifiers now, to change the size (or shape for that matter) of each hole, you only 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
2014-10-25 Loose version
2014-10-27 Ball stud changes
2014-10-27 3D spring for 3D0234 delta effector rod
2014-10-27 Delta rod spring
2014-10-29 New MCU Conversion
    AT90 is hooked up in schematic
2014-10-30 adding .gcode to .gitignore
2014-10-30 Added CONN-OSTTA020161 to Firepick.lbr
2014-10-30 EMC01 Revision B: Added +5V voltage regulator and other misc stuff
2014-10-30 *.l** added
2014-10-30 Updating PDFs for Rev B EMC01
2014-10-30 Updates to EAT0001 (Rev. A)
2014-10-30 Adding new files. Assembly isn't usable, just checking in before merge...
2014-10-31 minor cosmetic and refdes updates
2014-11-01 Pi wedge
2014-11-01 Wedge prototype
2014-11-02 Camera hacks
2014-11-04 RPiCam mount
2014-11-04 M2Nut Trap
2014-11-04 Nut trap, broken assembly
2014-11-05 Plate
2014-11-05 Tweak
2014-11-06 Sizing
2014-11-06 Effector STL
2014-11-06 Minor tweaks for usability
2014-11-08 split notch
2014-11-09 Eliminate catenary spring rattle by reducing hole size
2014-11-10 Modify bearing block to accept Nylock nuts
    Also adds a bit of strength to stop nut tearing it's mounting out.
2014-11-10 Rename
2014-11-10 Revert "Modify bearing block to accept Nyloc nuts"
2014-11-12 Better catenary springs
2014-11-12 Vacuum coupling; ROM mods for rods
2014-11-13 N8 mount
2014-11-14 README
2014-11-14 image
2014-11-14 Nema8
2014-11-14 LC1005
2014-11-14 LC1005 -> 3DLC10005
2014-11-16 Extrusion washer; Vacuum shaft coupling
2014-11-18 3DLC0456
2014-11-18 3DLC0454
2014-11-19 3D plates
2014-11-20 Tubing Tool and End Cap
2014-11-20 PC04; Hack cleanup
2014-11-20 PC04
2014-11-20 M8 removal
2014-11-20 DXF for Igor
2014-11-21 T Handle
2014-11-21 Delta arm with shaft
2014-11-22 3DLC0002
2014-11-22 3DLC0051A
2014-11-23 Limit switch interruptor
2014-11-23 limit
2014-11-23 Arm collision fix
2014-11-24 Print support
2014-11-27 Effector plate
2014-11-27 Vertical print
2014-11-28 bearing lbock
2014-11-30 STEP and SAT files
2014-11-30 STEP file conversion
2014-12-11 work
2015-04-04 updating STLs
2015-04-04 deleted
2015-04-11 added brim and fixed bridging issue
2015-04-13 reverting back to 9991c084dfd11b766cb2ae2e9ac17f71bdc60d1a
2015-05-06 Checkin of mostly-production-ready files
2015-05-06 Removing STL's from mechanical (moving them to 'production files' dir)
2015-05-06 baleted
2015-05-06 Moving STL's over here
2015-05-06 Initial check-in of the packing list for FPD beta kits
2015-05-06 new boards,
2015-05-06 forgot to check you in
2015-05-08 Fixed frame mounting screw hole. Reverting back to M5 hardware from M3X which didn't work as expected... The M3X needs more work before it can be re-introduced.
2015-05-08 Adding new stuff!
2015-05-14 new stuff, checking in before bay area trip
2015-06-03 Adding schematic and fabrication drawing PDFs
2015-06-04 Updated the EMC02 schematic PDF to include the second page
2015-06-13 Revised Laser Tool
    -Updated to laser heat sink with built in protection in the laser head.
    -Added more fins around area where fans blow air
    -Renamed files to suit convention
    -Added PCB Assemblies
    -Added Eagle files
2015-06-13 Gernerated pdf files
2015-06-29 Laser Schematic + PCB Update
    Added 30 mm fan mounts + connector
    Changed values to suit mods on prototype
    Added switchmode PSU enable line to global enable line to stop current
    flowing
    Added more TODO:'s to schematic
    Added copper pours on both sides of PCB
2015-07-11 Further schematic updates
    - updated comments on schematic
    - added credit to crow + license terms
    - generated pdf's
